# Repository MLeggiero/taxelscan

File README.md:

# TaxelScan v4

Reader board for a 32 × 32 carbon-nanotube tactile mat. Up to eight boards
share one RS-485 harness, start every frame on the same edge, and reach the
host through the first board's USB-C port.

> **Status, 8 Oct 2026:** designed and verified in KiCad. DRC and
> schematic parity are clean, every IC has been checked against its
> datasheet, and the analog chain and USB hot plug have been simulated.
> Fabrication and assembly files are ready; the board is not yet built and
> its firmware not yet written. Every number below is a design value or a
> datasheet value, not a measurement.

| Top | Bottom |
|:---:|:---:|
|  |  |

Plan-view renders of `boards/rev4/rev4.kicad_pcb`, 60.3 × 35.9 mm.

## Key numbers

| | |
|---|---|
| Taxels | 32 × 32 = 1,024 per board; 8,192 on an 8-board harness |
| Converter | the RP2354A's 12-bit SAR ADC, both banks in round robin, 500 ksps |
| Noise *(predicted)* | 1.6–2.3 LSB rms per conversion (ENOB 9.0–9.5) ≈ 8.1–8.6 noise-free bits; the front end adds 0.13 LSB rms |
| Frame rate *(predicted)* | 60 Hz target for 8 boards; 10.9 ms scan, 92 fps ceiling |
| Controller | RP2354A: 2 × Cortex-M33 at 150 MHz, 520 kB SRAM, 2 MB flash in package |
| Board | 60.3 × 35.9 × 1.6 mm, 4 layers, all parts on top |
| Parts | 102 placed (104 on the two end boards), 69 BOM lines, about $15 per board |

## Signal chain

| Stage | Value | Part |
|---|---|---|
| Row drive | 32 rows on the 3.3 V rail; unselected rows held at 0 V | 4 × SN74LVC595A |
| Column select | 2 banks × 16 columns | 2 × CD74HC4067 |
| Sensor, design basis | 1 MΩ at rest, 50 kΩ pressed (assumed) | CNT film |
| Pulldown | 10 kΩ, 0.1 %, 25 ppm/°C | R1, R2 |
| Sense node | 25 mV at rest, 435 mV pressed | |
| Gain | × 6 (10 kΩ / 2 kΩ) | TLV9062 |
| ADC input | 149 mV at rest, 2.61 V pressed; 51 Ω + 1 nF C0G (51 ns) | R21/R22, C31/C32 |
| Reference | ADC_AVDD: the 3.3 V rail through 10 Ω + 100 nF. The rows run from the same rail, so the reading is ratiometric | R26, C36 |
| Converter | 12 bits, ENOB 9.0 min / 9.5 typ; bank A on ADC1 (GPIO27), bank B on ADC3 (GPIO29); the rail monitor on ADC2 | RP2354A |
| 1 LSB | 806 µV at the ADC, 134 µV at the sense node | |
| Counts | about 185 at rest and 3,228 pressed; clipping below 38 kΩ | |
| Settling *(predicted)* | 5.0–6.6 µs to 0.5 LSB with 20 pF of column capacitance | |

## Timing *(predicted)*

| Step | Time |
|---|---|
| One conversion | 2 µs |
| One mux channel, both banks: 6.6 µs settle, a discard and a read per bank, firmware overhead | 19.4 µs |
| One row, 16 channels | 0.32 ms |
| One frame: 32 rows + 2 dark sweeps | 10.9 ms with 20 pF columns (92 fps); 12.0 ms with 50 pF (83 fps) |
| Conditioning 1,024 taxels, second core | ≈ 3.5 ms |
| Sensor to host at 60 Hz | ≈ 22 ms + USB |

## Chain

| | |
|---|---|
| Boards per harness | 8, addressed by 3 solder jumpers (all closed = address 0) |
| Harness | JST GH 6-way (GHR-06V-S housings, SSHL-002T-P0.2 contacts), 26 AWG, 1 A, 4 m planned |
| Wiring | pin n to pin n, from J3 of one board to J4 of the next; J3 and J4 are turned 180° to each other, so the wires cross between boards. Pin 1 is marked at both |
| Pinout | 1 +5 V · 2 GND · 3/4 DATA+/− · 5/6 SYNC+/−, the two pairs twisted |
| Transceivers | 2 × SN65HVD75: 20 Mbps, ±12 kV IEC 61000-4-2 on the bus pins |
| Data pair | half duplex, master polls; 12.5 Mbaud planned (PIO UART), 3 Mbaud for bring-up |
| Sync pair | master sends a 100 µs pulse per frame; every board starts on its falling edge |
| Termination | 120 Ω on the two end boards only |
| Frame size | 1,676 B with a 12-bit map · 140 B contacts only |
| 8 boards at 60 Hz | 804 kB/s with 12-bit maps; the bus 63 % busy |

## Power

| | |
|---|---|
| Input | 5 V from USB-C or the harness, diode-OR (PMEG2005AEA) |
| 3.3 V rail | TPS62162 buck, fixed 3.3 V (3.18–3.43 V); 3–17 V in, 20 V absolute maximum |
| Core rail | RP2354A internal buck with a 3.3 µH AOTA-B201610S3R3, laid out as Raspberry Pi's RP2350A minimal design |
| Draw *(estimate)* | 16–28 mA per board at 5 V, plus about 25 mA while a board transmits |
| Harness feed from USB | 321 mA (285–363) on a 500 mA port; 632 mA (576–697) on a 1.5 A or 3 A Type-C source |
| Boards per feed | 8 on a 500 mA port: seven downstream boards and one transmitter draw 140–225 mA |
| Far end | the eighth board's buck sees about 3.7–4.0 V from a 4.75 V source; it needs 3.3 V |
| Protection | USBLC6-2P6 on D+/D−/VBUS · 0.68 Ω + 22 µF hot-plug damper · PMEG2010ER reverse block |

## Build

| | |
|---|---|
| PCB | JLCPCB, 4 layers, JLC04161H-7628, 1.6 mm, 1 oz outer |
| Rules | 0.10 / 0.10 mm trace/space in the fine-pitch areas, 0.15 / 0.15 elsewhere (four slow nets keep 45 mm at 0.10 mm); copper 0.40 mm from the edge; 300 vias, 0.30 mm drill / 0.50 or 0.60 mm pad |
| Vias | tented: no via hole in an SMD pad but the 9 in U9's and U12's exposed pads and one at U5, so epoxy filling and capping is optional ([design review](boards/rev4/REVIEW.md)) |
| Assembly | Standard PCBA, top side, 0201 smallest; resistors thin film 0.1 %, 25 ppm/°C |
| Files | `boards/rev4/fab/`: `rev4-gerbers.zip`; `rev4-bom.csv` + `rev4-cpl.csv` (102 parts); `-end` pair (104 parts, adds 2 × 120 Ω) |
| Parts cost | about $15 per board for 10 boards at JLCPCB part prices (an estimate, not a quote); PCB and assembly fees extra |
| Programming | USB-C with a BOOTSEL button, or SWD on a 2.54 mm 1 × 4 header in Raspberry Pi's debug order (SC, GND, SD, RUN) |

Order options and what to check in the placement preview:
[`boards/rev4/fab/ORDER-NOTES.txt`](boards/rev4/fab/ORDER-NOTES.txt).

## Verify

```bash
cd boards/rev4
python gen_rev4.py      # writes rev4.net and BOM.csv, asserts every net
python check_faults.py  # injects 41 faults, each must be caught
python make_fab.py      # gerbers, drills, BOM, CPL, drawings
```

| Check | Result |
|---|---|
| Netlist assertions | 134 / 134 nets |
| Fault injection | 42 / 42 behave (41 faults + clean baseline) |
| ERC | 0 errors |
| DRC, zones refilled, schematic parity | 0 unconnected, 0 copper errors |
| Functional review | every IC against its datasheet, the analog chain and hot plug in ngspice: [`boards/rev4/VERIFICATION.md`](boards/rev4/VERIFICATION.md) |

## Open items

| Item | Value to confirm |
|---|---|
| Sensor pressed resistance | 50 kΩ assumed; sets R1/R2 and the gain |
| Column capacitance (mat + FFC) | unmeasured; a 6 µs settle covers about 20 pF |
| ADC noise and bank-to-bank carry-over | raw σ at rest, and whether a conversion must be discarded after each bank switch |
| Hot plug | +5V_USB and the buck input from the stiffest supply; simulated ≤ 6.78 V and ≤ 6.50 V |
| Core rail | VCORE at DVDD pin 23 under load steps, 1.05–1.16 V |
| USB throughput, 8 × 12-bit maps | 804 kB/s against a ≈ 1 MB/s CDC ceiling |
| Firmware | not written; specification in [`firmware/rev3/PLAN.md`](firmware/rev3/PLAN.md), which needs this board's ADC pin map (GPIO27 / 29) |

The smaller items, and what to measure at bring-up, are in
[`boards/rev4/VERIFICATION.md`](boards/rev4/VERIFICATION.md).

Do not flash `firmware/taxelscan/` to this board. It is an earlier board's
sketch and drives GPIO22/23, which are an address strap and the power-fault
input here.

## Repository

```text
boards/rev4/          the board: KiCad project, netlist generator, fab/ package, verification
firmware/rev3/        firmware specification
firmware/rev3_power/  USB power policy, written and unit-tested
libraries/            shared symbols, footprints and 3D models
boards/rev3/, boards/rev1/, firmware/taxelscan/, boards/v2-*/   earlier boards and their firmware
```

`tmp/` and `boards/rev3/backups/` are local working folders and are not in the
repository.

## Credits and license

Sensor pads, electrode geometry and the original readout topology come from the
FlexiTac project. MIT licensed; see [LICENSE](LICENSE).

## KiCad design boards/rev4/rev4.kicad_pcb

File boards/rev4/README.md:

# rev-4 — rev-3 without the external ADC

rev-4 is the rev-3 board (one mat per board, eight boards per harness) with
the LTC1865L 16-bit converter taken out. Both sense banks are read by the
RP2354A's own 12-bit ADC. Everything else — the row drive, the muxes, the ×6
gain stage, the RS-485 harness, the USB-C power path — is rev-3's, at rev-3's
positions, on rev-3's 60.3 × 35.9 mm outline.

| file | what it is |
|---|---|
| `gen_rev4.py`, `check_faults.py` | the netlist generator with its assertions, and the fault-injection proof that they bite (41 faults, all caught). `./gen_rev4.py` writes `rev4.net` and `BOM.csv` |
| `rev4.kicad_pro`, `rev4.kicad_sch`, `rev4.kicad_pcb`, `rev4.kicad_dru`, `fp-lib-table`, `sym-lib-table`, `TaxelScanPower.kicad_sym` | the KiCad 10 project |
| `rev4.net`, `BOM.csv` | generated: the netlist and the bill of materials with LCSC numbers and notes |
| `gen_schematic.py`, `layout_schematic.py`, `make_fab.py`, `kicad_tools.py` | the schematic generator and its drawing, the JLCPCB exporter, pcbnew helpers — rev-3's, retargeted |
| `fab/` | the JLCPCB package from `make_fab.py`: gerbers, drills, `rev4-gerbers.zip`, middle-board and end-board BOM/CPL sets, drawings, order and stackup notes |
| `jlc_placement.csv` | the rotation and origin offset JLCPCB needs for each part, fitted by `tools/jlc_placement.py` from the LCSC parts' own footprints; `make_fab.py` applies it to the CPLs |
| `PLACEMENT.md` | the placement analysis: what removing U8 freed, every move considered, which were made and why |
| `ROUTING_STATUS.md` | the routed board: how it was re-routed for straight routing, DRC, parity, plane health, open items |
| `REVIEW.md` | the 21 October design review: an experienced electrical engineer's six comments on the layout, each measured on the board, and what changed for the ones that hold |
| `VERIFICATION.md` | the functional check: every IC against its datasheet, the analog chain and hot plug simulated, the layout measured, what to fix before ordering and what to measure at bring-up (scripts in `verify/`) |
| `tools/` | the board-change, placement and routing scripts for this revision, and rev-3's router ported to run anywhere (see `tools/README.md`) |
| `pcb_top.png`, `pcb_rev3_vs_rev4.png`, `pcb_routing_before_after.png`, `pcb_review_vias.png` | renders: the board, the ADC corner against rev-3, the routing before and after the re-route, the plane vias before and after the design review |
| `../../libraries/TaxelScan.3dshapes/` | U9's 3D model. KiCad ships none for the QFN-60, so `make_qfn60.py` draws it from the package drawing in the RP2350 datasheet (Fig. 147): 60 leads, one on each pad. J5 shows KiCad's GCT USB4105 body, whose pads match the HRO part's to 0.05 mm |

The design record for everything this revision did not touch — the front-end
reasoning, the USB power design, the audits, the routing history — is in
`../rev3/`, and is not repeated here.

## What changed from rev-3

**Five parts removed.**

| Ref | Part | Job in rev-3 |
|---|---|---|
| U8 | LTC1865LIMS, dual 16-bit SAR, MSOP-10 | the converter, on SPI0 |
| C8 | 1 µF 0402 | U8's VCC bypass |
| R10 | 10 Ω 0402 | U8's reference filter, tapped off ROW_VCC |
| C10 | 10 µF 0805 | the reference reservoir |
| C26 | 10 nF C0G 0402 | the reference's high-frequency bypass |

Parts placed: **109 → 104** on a middle board, **111 → 106** on the two end
boards. Distinct part numbers: **49 → 47** — only the LTC1865LIMS (C580457)
and the 10 nF C0G (C22400107) disappear from the order; C8, R10 and C10 shared
reels with C41, R26 and C9/C39/C46. The low-stock line in rev-3's order notes
(the LTC1865LIMS, 23 in stock) is gone.

**Parts cost.** rev-3's $33.08 per board (10 boards at JLCPCB prices, 28
September 2026) included $18.47 for the LTC1865L. Without it rev-4's parts come
to about **$14.60** a board; the other four parts that went are cents. That is
rev-3's figure less U8's line, not a fresh quote.

**Five nets removed:** `VREF`, `ADC_CONV`, `ADC_SCK`, `ADC_SDI`, `ADC_SDO` —
140 → 135 nets.

**The pin map.** The internal ADC's inputs are GPIO26–29. GPIO26 still cannot
escape (C35, as in rev-3), so:

| signal | rev-3 | rev-4 |
|---|---|---|
| `ADC_A` (bank A) | U8 CH0 | **GPIO27 / ADC1, pin 41** |
| `ADC_B` (bank B) | U8 CH1 | **GPIO29 / ADC3, pin 43** |
| `RAIL_MON` | GPIO28 / ADC2 | GPIO28 / ADC2 (unchanged) |
| `USB_CC_OUT1` | GPIO27 | **GPIO18** (rev-3's `ADC_SCK`) |
| `USB_CC_OUT2` | GPIO29 | **GPIO19** (rev-3's `ADC_SDI`) |
| GPIO16, GPIO17 | `ADC_SDO`, `ADC_CONV` | unused |

`firmware/rev3_power/usb_power_policy.h` takes `-DTAXELSCAN_BOARD_REV=4` for the
rev-4 USB-C pins, and its native test checks both maps at compile time.

**Placement.** Seven parts moved, all in one corner east of the MCU: the two
ADC-input cells (R21/C31, R22/C32) from beside U8 to beside the RP2354A's ADC
pins, and the rail monitor (R15/R16/C45) out of their way. U7 and the gain
network, the muxes, the MCU, the connectors and the outline did not move;
`PLACEMENT.md` has the analysis, including the two moves that were considered
and rejected (moving U7 west, and re-compacting the outline for 0.9 mm). After
the verification, the regulator and buck corners were re-placed and R30 / R31
moved (below).

**Silkscreen.** The back reads `TaxelScan v4`, so the two revisions can be
told apart on the bench. The front has gained a `1` at pin 1 of J3 / J4 and
J6's `SC GND SD RUN` (below).

**Routing.** Re-routed from scratch so that every track runs at 0, 45 or 90
degrees: rev-3's routing, which the first rev-4 kept, had 67 % of its copper at
arbitrary angles; now 0.03 % (0.8 mm of plane ties). Freerouting did the bulk.
The 30 nets it cannot be trusted with were laid first by the board's own
exact-geometry router, octilinear, which also finished and tidied what
Freerouting left:
- the RS-485 pairs and both USB pairs (the USB-C side bridged across J5's
  interleaved pins and run side by side);
- the core regulator as Raspberry Pi lay it out, the buck's input loop, VCORE,
  VREG_LX and SW_NODE;
- the ADC corner, the crystal, J5's VBUS pins and USB_ILIM;
- the corner south and east of the RP2354A, with its address lines, debug
  lines and TUSB320 nets.

Nothing routes on In2 any more (it had 125 mm), so the +3.3 V plane is one
piece. The 5 V rails are 0.3 mm, widened to 0.5-0.6 mm where they fit (bar
D5.5's VBUS tie at 0.15 mm), and VCORE is 0.2 mm.
`ROUTING_STATUS.md` has the method and every number; `pcb_routing_before_after.png`
shows it.

**Rules.** The `U8_escape` rule area and its two custom rules are gone. Six
spots near R22 and D4 had been legal only at that area's 0.10 mm; R22 moved,
and the `USB_ILIM` / `USB_ILIM_LOW` segments were re-routed at the board's
0.15 mm.

## Fixed after the verification (7 October 2026)

`VERIFICATION.md` found three things to deal with before ordering, none of them
new in rev-4, and two smaller ones that were cheap to fix with them. All are
done; the board was re-placed in those two corners (`tools/fix_rev4.py`) and
re-routed from scratch.

**The core regulator, laid out the way Raspberry Pi lay it out** (finding 1).
The RP2350 datasheet (§6.3.8) asks for its Figure 26 "as closely as possible";
rev-3's CIN and COUT sat 5.7–5.9 mm from the pins. Now the parts are at the
offsets from pins 46–50 that Raspberry Pi's RP2350A minimal design uses:

- C44 (CIN) straddles VREG_VIN (pin 49) and VREG_PGND (pin 47); C19 (COUT) is
  beside it; L1 is above, its polarity dot on VCORE. Both capacitors are now
  0402 4.7 µF (Samsung CL05A475MP5NRNC; the minimal design fits Murata's 6.3 V
  GRM155R60J475ME47D) on the minimal design's wide-gap land
  (`FlexiTac:C_0402_1005Metric_WideGap`), so VREG_LX runs straight up from pin
  48 between their pads into L1: 3.3 mm on F.Cu with no via (it was 4.4 mm).
- CIN's and COUT's grounds join pin 47 and reach the plane at one point,
  through two adjacent vias. CFILT (C43, now 0402 too) has its own ground via.
  VREG_FB is taken from COUT's pad, beside LX rather than under it. VCORE
  leaves through two vias west of COUT. In1 is cut away under L1 and the LX
  track (Figure 27).
- The switching loop, LX → L1 → COUT → ground → PGND, encloses 2.6 mm²
  (`verify/layout/vreg_loop.py`), against about 20 mm² before and 2.3 mm² in
  the minimal design measured the same way.
- R23 / R24, the USB series resistors, moved north-west of pins 51 / 52 as in
  the minimal design, so USB_D leaves on F.Cu with no via: 4.1 / 3.8 mm,
  where it was 5.7 / 4.8 mm through two vias each.
- Pins 53 and 54 (USB_OTP_VDD, QSPI_IOVDD) are tied in the ring and share C18,
  1.3 mm of track from pin 54 with its own ground via. That also settles
  finding 4. C17, no longer needed at VREG_VIN,
  decouples the VREG_AVDD filter's +3.3 V input.

**Hot plug** (finding 2). The new simulation (`verify/power/damper.py`) took
the supply to USB-C's 5.5 V maximum. There, with a 1.5 µH captive cable, the
old damper left U12's input at 7.06 V against the TLV62569's 6 V absolute
maximum, and +5V_USB at 7.36 V against U14's 7 V. No damper inside USB's
attach-capacitance limits keeps a 6 V part safe, so:

- U12 is now TI's TPS62162 (LCSC C40256): the fixed 3.3 V member of the
  TPS6216x, 3–17 V in, 20 V absolute maximum. It runs at 100 % duty cycle at
  the far end of the harness and has the same 2.2 µH / 22 µF output as before
  (TI's standard pairing). The fixed output takes R18 / R19 off the board.
  It is laid out as TI's Figure 42: C27 across VIN / PGND at the pins, C22
  beside them, AGND, PGND and C22's ground meeting at the exposed pad (two
  vias), L2 beside SW (2.5 mm of 0.3 mm track, was 4.3 mm), VOS from L2's
  output pad.
- The damper is now R38 0.68 Ω + C46 22 µF (the C23 reel). +5V_USB stays at
  or below 6.78 V in every case simulated: 5.0–5.5 V supplies, 0.5–2 µH
  cables. That is inside U14's 7 V. U12's input now peaks at 6.5 V against
  20 V. The cost is about 5 µF more effective attach capacitance, behind 0.68 Ω.

**The harness cable** (finding 3). J3 and J4 are the same part turned 180° to
each other, so a cable laid straight across between two boards joins pin 1 to
pin 6. That puts +5V_BUS on SYNC_N, and the next board gets no power. The
cable is:

| J3 / J4 pin | net | cable |
|---|---|---|
| 1 | +5V_BUS | marked `1` on the silkscreen at both connectors |
| 2 | GND | |
| 3 / 4 | BUS_P / BUS_N | twisted pair |
| 5 / 6 | SYNC_P / SYNC_N | twisted pair |

It uses JST GH parts: a GHR-06V-S housing at each end, SSHL-002T-P0.2
contacts and 26 AWG wire. It is wired **pin n to pin n**, from J3 of one board
to J4 of the next, so the wires cross between adjacent boards. Ring J3.1 to
J4.1 before connecting power. The end boards carry R11 / R12 (the `-end` CPL).

**The debug header** (finding 10). J6 is now SWCLK, GND, SWDIO, RUN (pins
1–4): Raspberry Pi's 3-pin debug connector order (SC, GND, SD) on pins 1–3,
so the Debug Probe's lead fits pin 1 to pin 1. The silkscreen reads
`SC GND SD RUN` above the pins.

**Firmware** (finding 11). `firmware/rev3_power/usb_power_policy.h` no longer
defaults to rev-3. It stops the build with `#error` unless
`TAXELSCAN_BOARD_REV` is 3 or 4.

**For the re-route**, R30 / R31 (U14's EN pull-down and FAULT pull-up) moved
from west of U9 to under U14's pins 3 and 4. Where rev-3 left them, both nets
crossed under the MCU to reach them (38–52 mm, 4–6 vias), and the rip-up loop
could not fit them past U9's east side. Now they are 20 and 26 mm, with 2 vias
and none.

Placed parts: 104 → 102 on a middle board, 106 → 104 on the two end boards. Nets: 135 → 134 (`FB` went with the divider).
Distinct part numbers: 47 → 46.

## What the internal ADC changes, electrically

- **The reference.** The RP2350-family ADC has no reference of its own and
  converts against its supply pin, `ADC_AVDD`. Here that is +3.3 V through R26
  (10 Ω) with C36 (100 nF) at the pin; ROW_VCC, the row excitation, is +3.3 V
  through R5 (0 Ω). Reference and excitation are two branches of one rail, so
  the reading stays ratiometric, as rev-3's ROW_VCC-tapped VREF made it. The ADC
  draws about 150 µA from `ADC_AVDD` (Raspberry Pi's Pico 2 datasheet quotes the
  30 mV this costs across that board's 201 Ω filter), so R26's drop is ~1.5 mV:
  a fixed 0.05 % gain error, small beside the 0.1 % resistors that set the
  gain. rev-3's R10/C10 held its reference quiet above ~1.6 kHz; R26/C36 corner
  at ~160 kHz, so the reference now tracks the excitation over a wider band -
  rail noise common to both cancels instead of appearing in the reading - while
  R26 still keeps IOVDD switching noise off it.
- **Resolution.** `../rev3/ROUTING_STATUS.md` estimated the 16-bit chain at
  ~11.9 noise-free bits at 80 fps. The internal ADC's ENOB is 9.0 minimum,
  9.5 typical (RP2350 datasheet Table 1685): 1.6-2.3 LSB rms, 8.1-8.6 noise-free
  bits per conversion. That is 10-14× more noise per conversion than rev-3
  expected, before oversampling and the conditioning filters - the same converter
  rev-1, the board that has shipped, reads its mat with. The front end adds only
  0.13 LSB rms (`VERIFICATION.md`). The ×6 gain stage, which is where rev-3's
  sensitivity gain over rev-1 comes from, stays.
- **One converter for both banks.** The internal ADC is a single SAR behind an
  input mux, as on rev-1, where reading bank A then bank B let charge carry over
  and the firmware's `adcDiscard` throws one conversion away after a switch.
  rev-1 had nothing at the pins; here each pin has its 1 nF reservoir, far
  larger than the sampling capacitor, so the carried charge is shared into the
  reservoir instead of landing on a bare high-impedance node. Keep `adcDiscard`
  until bring-up measures it (rev-1's test 0c).
- **Firmware.** No LTC1865L driver to write: `firmware/rev3/PLAN.md` §3.3 and the
  SPI0 transfer sequence fall away. Its count domain (D2) already scales the
  16-bit code down to rev-1's 12-bit count, 806 µV at the ADC, so the internal
  ADC gives the same count with `adcShift = 0`, and the conditioning pipeline and
  the simulator's golden digest are unaffected. rev-1's `scan.cpp` internal-ADC
  path carries over with the new channels (ADC1 / ADC3).

## How it was built, and what was checked

    ./gen_rev4.py                  rev4.net + BOM.csv: 134 of 134 nets check out
    ./check_faults.py              41 injected faults all caught, clean baseline passes (42 of 42)
    ./gen_schematic.py             rev4.kicad_sch: 134 of 134 nets match, before and after the
                                   KiCad 10 upgrade; 107 parts agree with BOM.csv; ERC 0 errors
    tools/eco_rev4.py              rev3.kicad_pcb -> rev4.kicad_pcb: rip, delete, re-pin
    tools/place_rev4.py            the seven moves, each placed and routed
    tools/route_rev4.py            AMP_A/B, +5V, USB_CC_OUT1/2, the ILIM fixes, FID2; prune
    tools/fix_rev4.py              the verification fixes: regulator corner, TPS62162, J6, silk; R30 / R31
    tools/freeroute_rev4.py all    the re-route: strip, pre-route, freerouting, import, finish
    tools/review_rev4.py           the design review's changes (REVIEW.md): edge, vias, widths, corners
    tools/finalize_rev4.py         install, then KiCad DRC with zones refilled + schematic parity
    ./make_fab.py                  fab/

| Check (KiCad 10.0.7) | Result |
|---|---|
| DRC, zones refilled | 0 unconnected, 0 copper errors under the design review's rules (copper 0.40 mm from the edge, via holes 0.10 mm clear of SMD pads, 0.15 mm track outside the escape areas); rev-3's same 5 silkscreen warnings |
| Schematic parity | every net's pads match; the only items are rev-3's net-name prefix and J5's two open SBU pins |
| ERC | 0 errors |
| Routing | 0.8 of 2306 mm (0.03 %) off 0 / 45 / 90 degrees, all of it plane ties (first rev-4: 67 %); nothing on In2; 169 signal vias; no via hole in an SMD pad but the exposed pads' 9 (U5 pin 15's pad toe cut back 0.30 mm, 26 October); 8 bare right angles, none on the pairs; the USB-C data pair 2 / 2 vias, side by side |
| +3.3 V plane (In2) | 1 piece, 1840 mm², all 31 vias (the 8 October board, filled the same way with KiCad 10.0.7: 1841 mm²; first rev-4: 2 pieces, 1740 mm², 33 of 34; rev-3: 7 pieces, 1665 mm², 27 of 35) |
| GND plane (In1) | one piece, 1875 mm², all 100 vias (8 October, filled the same way: 1879 mm², 104 vias) |
| Fab package | 69 BOM lines, every one with an LCSC number; 102 / 104 parts in the CPLs; both planes in the gerbers |
| Firmware pin map | `firmware/rev3_power` native test passes for rev-3 and rev-4; a build without `TAXELSCAN_BOARD_REV` stops |

What is still open, and what to measure at bring-up: `VERIFICATION.md` and `ROUTING_STATUS.md`.

The board scripts run with KiCad's Python (`pcbnew`); `tools/README.md` says how.
The intermediate boards live in `<checkout>/tmp/` (git-ignored).

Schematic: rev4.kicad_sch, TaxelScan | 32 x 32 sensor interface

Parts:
C1, C2, C3, C4, C5, C6, C7, C12, C27, C28, C29, C38, C40, C42, C45: 100nF; C_0402_1005Metric
C9, C39: 10uF; C_0805_2012Metric
C11, C13, C14, C15, C16, C17, C18, C24, C25, C33, C34, C35, C36: 100nF; C_0201_0603Metric
C19, C44: 4.7uF; C_0402_1005Metric_WideGap
C20, C21: 15pF; C_0402_1005Metric
C22: 4.7uF; C_0603_1608Metric
C23, C46: 22uF; C_0805_2012Metric
C31, C32: 1nF; C_0402_1005Metric
C37: 1uF; C_0805_2012Metric
C41: 1uF; C_0402_1005Metric
C43: 4.7uF; C_0402_1005Metric
D1, D2: PMEG2005AEA; D_SOD-323
D3: LED_Green; LED_0603_1608Metric
D4: PMEG2010ER; Nexperia_CFP3_SOD-123W
D5: USBLC6-2P6; SOT-666
J1, J2: FFC_32P_0.5mm; FFC_0.5mm_FH12_32_16_12way_Composite
J3, J4: Bus_6P; JST_GH_SM06B-GHS-TB_1x06-1MP_P1.25mm_Horizontal
J5: USB-C; USB_C_Receptacle_HRO_TYPE-C-31-M-12
J6: SWD; PinHeader_1x04_P2.54mm_Vertical
JP1, JP2, JP3: ADDR; SolderJumper-2_P1.3mm_Bridged_Pad1.0x1.5mm
L1: AOTA-B201610S3R3-101-T; L_0806_2016Metric
L2: 2.2uH; L_1210_3225Metric
Q1: 2N7002PW; SOT-323_SC-70
R1, R2, R6, R8, R20, R31, R32, R33, R37: 10k; R_0402_1005Metric
R3, R4, R35: 33R; R_0402_1005Metric
R5: 0R; R_0402_1005Metric
R7, R9: 2k; R_0402_1005Metric
R11, R12: 120R; R_0603_1608Metric
R15: 100k; R_0402_1005Metric
R16: 47k; R_0402_1005Metric
R17, R25, R36: 1k; R_0402_1005Metric
R21, R22: 51R; R_0402_1005Metric
R23, R24: 27R; R_0402_1005Metric
R26: 10R; R_0402_1005Metric
R27, R28: 82.5k; R_0402_1005Metric
R29, R30: 4.7k; R_0402_1005Metric
R34: 866k; R_0402_1005Metric
R38: 0.68R; R_0603_1608Metric
SW1: BOOTSEL; SW_SPST_B3U-1000P
U1, U2, U3, U4: SN74LVC595APW; TSSOP-16_4.4x5mm_P0.65mm
U5, U6: CD74HC4067SM96; SSOP-24_5.3x8.2mm_P0.65mm
U7: TLV9062IDGKR; MSOP-8_3x3mm_P0.65mm
U9: RP2354A; QFN-60-1EP_7x7mm_P0.4mm_EP3.4x3.4mm
U10, U11: SN65HVD75DR; SOIC-8_3.9x4.9mm_P1.27mm
U12: TPS62162DSGR; Texas_DSG0008A_WSON-8-1EP_2x2mm_P0.5mm_EP0.9x1.6mm
U13: TUSB320LAIRWBR; Texas_X2QFN-12_1.6x1.6mm_P0.4mm
U14: TPS2553DBVR; SOT-23-6
Y1: ABM8-272-T3; Crystal_SMD_3225-4Pin_3.2x2.5mm

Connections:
+3.3V: C5.1, C6.1, C7.1, C9.1, C11.1, C12.1, C13.1, C14.1, C15.1, C17.1, C18.1, C23.1, C28.1, C29.1, C33.1, C34.1, C40.1, C41.1, C44.1, L2.2, R5.1, R20.2, R26.1, R31.2, R32.2, R33.2, R35.1, U5.24 (VCC), U6.24 (VCC), U7.8 (V+), U9.1 (IOVDD), U9.11 (IOVDD), U9.20 (IOVDD), U9.30 (IOVDD), U9.38 (IOVDD), U9.45 (IOVDD), U9.49 (VREG_VIN), U9.53 (USB_OTP_VDD), U9.54 (QSPI_IOVDD), U10.8 (VCC), U11.8 (VCC), U12.6 (VOS), U13.12 (VDD)
+5V: C22.1, C27.1, D1.1 (K), D2.1 (K), R15.1, U12.2 (VIN), U12.3 (EN)
+5V_BUS: C39.1, D1.2 (A), D4.1 (K), J3.1, J4.1
+5V_USB: C37.1, C38.1, C42.1, D2.2 (A), D5.5 (VBUS), J5.A4 (VBUS), J5.A9 (VBUS), J5.B4 (VBUS), J5.B9 (VBUS), R34.1, R38.1, U14.1 (IN)
ADC_A: C31.1, R21.2, U9.41 (GPIO27/ADC1)
ADC_AVDD: C36.1, R26.2, U9.44 (ADC_AVDD)
ADC_B: C32.1, R22.2, U9.43 (GPIO29/ADC3)
ADDR0: JP1.1 (A), U9.32 (GPIO20)
ADDR1: JP2.1 (A), U9.33 (GPIO21)
ADDR2: JP3.1 (A), U9.34 (GPIO22)
AMP_A: R6.2, R21.1, U7.1
AMP_B: R8.2, R22.1, U7.7
BOOTSEL: R25.1, U9.60 (~QSPI_SS)
BOOTSEL_SW: R25.2, SW1.1
BUS_DE: U9.14 (GPIO10), U10.2 (~RE), U10.3 (DE)
BUS_DI: U9.12 (GPIO8), U10.4 (DI)
BUS_N: J3.4, J4.4, R11.2, U10.7 (B)
BUS_P: J3.3, J4.3, R11.1, U10.6 (A)
BUS_RO: U9.13 (GPIO9), U10.1 (RO)
COL_0: J2.1, U5.9 (I0)
COL_1: J2.2, U5.8 (I1)
COL_2: J2.3, U5.7 (I2)
COL_3: J2.4, U5.6 (I3)
COL_4: J2.5, U5.5 (I4)
COL_5: J2.6, U5.4 (I5)
COL_6: J2.7, U5.3 (I6)
COL_7: J2.8, U5.2 (I7)
COL_8: J2.9, U5.23 (I8)
COL_9: J2.10, U5.22 (I9)
COL_10: J2.11, U5.21 (I10)
COL_11: J2.12, U5.20 (I11)
COL_12: J2.13, U5.19 (I12)
COL_13: J2.14, U5.18 (I13)
COL_14: J2.15, U5.17 (I14)
COL_15: J2.16, U5.16 (I15)
COL_16: J2.17, U6.9 (I0)
COL_17: J2.18, U6.8 (I1)
COL_18: J2.19, U6.7 (I2)
COL_19: J2.20, U6.6 (I3)
COL_20: J2.21, U6.5 (I4)
COL_21: J2.22, U6.4 (I5)
COL_22: J2.23, U6.3 (I6)
COL_23: J2.24, U6.2 (I7)
COL_24: J2.25, U6.23 (I8)
COL_25: J2.26, U6.22 (I9)
COL_26: J2.27, U6.21 (I10)
COL_27: J2.28, U6.20 (I11)
COL_28: J2.29, U6.19 (I12)
COL_29: J2.30, U6.18 (I13)
COL_30: J2.31, U6.17 (I14)
COL_31: J2.32, U6.16 (I15)
GAIN_A: R6.1, R7.1, U7.2 (-)
GAIN_B: R8.1, R9.1, U7.6 (-)
GND: C1.2, C2.2, C3.2, C4.2, C5.2, C6.2, C7.2, C9.2, C11.2, C12.2, C13.2, C14.2, C15.2, C16.2, C17.2, C18.2, C19.2, C20.2, C21.2, C22.2, C23.2, C24.2, C25.2, C27.2, C28.2, C29.2, C31.2, C32.2, C33.2, C34.2, C35.2, C36.2, C37.2, C38.2, C39.2, C40.2, C41.2, C42.2, C43.2, C44.2, C45.2, C46.2, D3.1 (K), D5.2 (GND), J1.MP (MountPin), J2.MP (MountPin), J3.2, J3.MP (MountPin), J4.2, J4.MP (MountPin), J5.A1 (GND), J5.A12 (GND), J5.B1 (GND), J5.B12 (GND), J5.SH (SHIELD), J6.2, JP1.2 (B), JP2.2 (B), JP3.2 (B), Q1.2 (S), R1.2, R2.2, R7.2, R9.2, R16.2, R27.2, R29.2, R30.2, R37.2, SW1.2, U1.8 (GND), U1.13 (~OE), U2.8 (GND), U2.13 (~OE), U3.8 (GND), U3.13 (~OE), U4.8 (GND), U4.13 (~OE), U5.12 (GND), U5.15 (~E), U6.12 (GND), U6.15 (~E), U7.4 (V-), U9.47 (VREG_PGND), U9.61 (GND), U10.5 (GND), U11.2 (~RE), U11.4 (DI), U11.5 (GND), U12.1 (PGND), U12.4 (AGND), U12.5 (FB), U12.9 (PAD), U13.3 (PORT), U13.10 (GND), U13.11 (~EN), U14.2 (GND), Y1.2 (G), Y1.4 (G)
LED_A: D3.2 (A), R17.2
MUX_S0: U5.10 (S0), U6.10 (S0), U9.7 (GPIO4)
MUX_S1: U5.11 (S1), U6.11 (S1), U9.8 (GPIO5)
MUX_S2: U5.14 (S2), U6.14 (S2), U9.9 (GPIO6)
MUX_S3: U5.13 (S3), U6.13 (S3), U9.10 (GPIO7)
RAIL_MON: C45.1, R15.2, R16.1, U9.42 (GPIO28/ADC2)
ROW_0: J1.1, U1.15 (QA)
ROW_1: J1.2, U1.1 (QB)
ROW_2: J1.3, U1.2 (QC)
ROW_3: J1.4, U1.3 (QD)
ROW_4: J1.5, U1.4 (QE)
ROW_5: J1.6, U1.5 (QF)
ROW_6: J1.7, U1.6 (QG)
ROW_7: J1.8, U1.7 (QH)
ROW_8: J1.9, U2.15 (QA)
ROW_9: J1.10, U2.1 (QB)
ROW_10: J1.11, U2.2 (QC)
ROW_11: J1.12, U2.3 (QD)
ROW_12: J1.13, U2.4 (QE)
ROW_13: J1.14, U2.5 (QF)
ROW_14: J1.15, U2.6 (QG)
ROW_15: J1.16, U2.7 (QH)
ROW_16: J1.17, U3.15 (QA)
ROW_17: J1.18, U3.1 (QB)
ROW_18: J1.19, U3.2 (QC)
ROW_19: J1.20, U3.3 (QD)
ROW_20: J1.21, U3.4 (QE)
ROW_21: J1.22, U3.5 (QF)
ROW_22: J1.23, U3.6 (QG)
ROW_23: J1.24, U3.7 (QH)
ROW_24: J1.25, U4.15 (QA)
ROW_25: J1.26, U4.1 (QB)
ROW_26: J1.27, U4.2 (QC)
ROW_27: J1.28, U4.3 (QD)
ROW_28: J1.29, U4.4 (QE)
ROW_29: J1.30, U4.5 (QF)
ROW_30: J1.31, U4.6 (QG)
ROW_31: J1.32, U4.7 (QH)
ROW_CLK: R3.2, U1.11 (SRCLK), U2.11 (SRCLK), U3.11 (SRCLK), U4.11 (SRCLK)
ROW_CLK_MCU: R3.1, U9.4 (GPIO2)
ROW_DATA: U1.14 (SER), U9.5 (GPIO3)
ROW_LATCH: R4.2, U1.12 (RCLK), U2.12 (RCLK), U3.12 (RCLK), U4.12 (RCLK)
ROW_LATCH_MCU: R4.1, U9.3 (GPIO1)
ROW_VCC: C1.1, C2.1, C3.1, C4.1, R5.2, U1.10 (~SRCLR), U1.16 (VCC), U2.10 (~SRCLR), U2.16 (VCC), U3.10 (~SRCLR), U3.16 (VCC), U4.10 (~SRCLR), U4.16 (VCC)
RUN: J6.4, R20.1, U9.26 (RUN)
SENSE_A: R1.1, U5.1 (COM), U7.3 (+)
SENSE_B: R2.1, U6.1 (COM), U7.5 (+)
SR_CHAIN_1: U1.9 (QH'), U2.14 (SER)
SR_CHAIN_2: U2.9 (QH'), U3.14 (SER)
SR_CHAIN_3: U3.9 (QH'), U4.14 (SER)
STATUS: R17.1, U9.37 (GPIO25)
SWCLK: J6.1, U9.24 (SWCLK)
SWDIO: J6.3, U9.25 (SWDIO)
SW_NODE: L2.1, U12.7 (SW)
SYNC_DE: R37.1, U9.17 (GPIO13), U11.3 (DE)
SYNC_N: J3.6, J4.6, R12.2, U11.7 (B)
SYNC_OUT: U9.15 (GPIO11), U11.1 (RO)
SYNC_P: J3.5, J4.5, R12.1, U11.6 (A)
USBC_D_N: D5.3 (I/O2), D5.4 (I/O2), J5.A7 (D-), J5.B7 (D-), R24.2
USBC_D_P: D5.1 (I/O1), D5.6 (I/O1), J5.A6 (D+), J5.B6 (D+), R23.2
USB_BUS_EN: R30.1, U9.36 (GPIO24), U14.3 (EN)
USB_BUS_SW: D4.2 (A), U14.6 (OUT)
USB_CC1: J5.A5 (CC1), U13.1 (CC1)
USB_CC2: J5.B5 (CC2), U13.2 (CC2)
USB_CC_OUT1: R32.1, U9.29 (GPIO18), U13.7 (SDA/OUT1)
USB_CC_OUT2: R33.1, U9.31 (GPIO19), U13.8 (SCL/OUT2)
USB_D_N: R24.1, U9.51 (USB_DM)
USB_D_P: R23.1, U9.52 (USB_DP)
USB_ILIM: R27.1, R28.1, U14.5 (ILIM)
USB_ILIM_HI: Q1.1 (G), R29.1, U9.2 (GPIO0)
USB_ILIM_LOW: Q1.3 (D), R28.2
USB_PWR_FAULT: R31.1, U9.35 (GPIO23), U14.4 (~FAULT)
USB_SNUB: C46.1, R38.2
USB_VBUS_DET: R34.2, U13.4 (VBUS_DET)
VCORE: C19.1, C24.1, C25.1, C35.1, L1.1, U9.6 (DVDD), U9.23 (DVDD), U9.39 (DVDD), U9.50 (VREG_FB)
VREG_AVDD: C16.1, C43.1, R35.2, U9.46 (VREG_AVDD)
VREG_LX: L1.2, U9.48 (VREG_LX)
XIN: C20.1, U9.21 (XIN), Y1.1
XOUT: C21.1, R36.2, Y1.3
XOUT_MCU: R36.1, U9.22 (XOUT)

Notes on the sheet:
TAXELSCAN / REV 4
32 x 32 matrix > two sense banks > RP2354A internal 12-bit ADC > RS-485 harness
01 ROW EXCITATION
MCU serial stream > four latched drivers > 32-way row FFC
02 COLUMN SENSING
32 columns > two 16:1 muxes > gain of 6 > filtered inputs to the MCU ADC
03 SCAN CONTROLLER
RP2354A / clock / core supply / local bypass
04 POWER + RAIL MONITOR
Harness or USB power > diode OR > local 3.3 V buck
05 COMMUNICATIONS + BOARD ADDRESS
Half-duplex data pair and dedicated receive-only sync pair
06 USB + PROGRAMMING
USB-C data / configuration straps / SWD / BOOTSEL
Rows 0-7
Rows 8-15
Rows 16-23
Rows 24-31
ROW FFC
Pin n = ROW_(n-1) Mounting pad = GND
Serial order: U1 > U2 > U3 > U4 Outputs enabled; unselected rows held LOW.
Clock / latch damping
U1-U4 bypass
Excitation rail link
COLUMN FFC
Pin n = COL_(n-1) Mounting pad = GND
R1/R2: 10k pulldown Rf/Rg: 10k / 2k (G = 6)
51R / 1nF at each MCU ADC pin Series resistors outside feedback
ADC_A > U9 GPIO27 / ADC1 (pin 41) ADC_B > U9 GPIO29 / ADC3 (pin 43)
The converter is the RP2354A (section 03). Its reference is ADC_AVDD, filtered off +3.3V by R26 / C36 (section 04); ROW_VCC is the same rail through R5, so the code stays ratiometric.
ROW_* > section 01 MUX_*, ADC_* > section 02 BUS_*, SYNC_* > section 05 USB_*, SWD* > section 06
Unused GPIO / stacked-flash pins are marked with no-connects.
R36: 1k XOUT series, limits crystal drive
12 MHz / C0G load capacitors
VREG_AVDD: 33R / 4.7uF filter
Core regulator / DVDD bypass
MCU 3.3 V bypass
3.3 V buck: TPS62162, fixed output 3-17 V in, 20 V absolute maximum
5 V rail monitor 100k / 47k divider to MCU
MCU ADC supply and reference filter

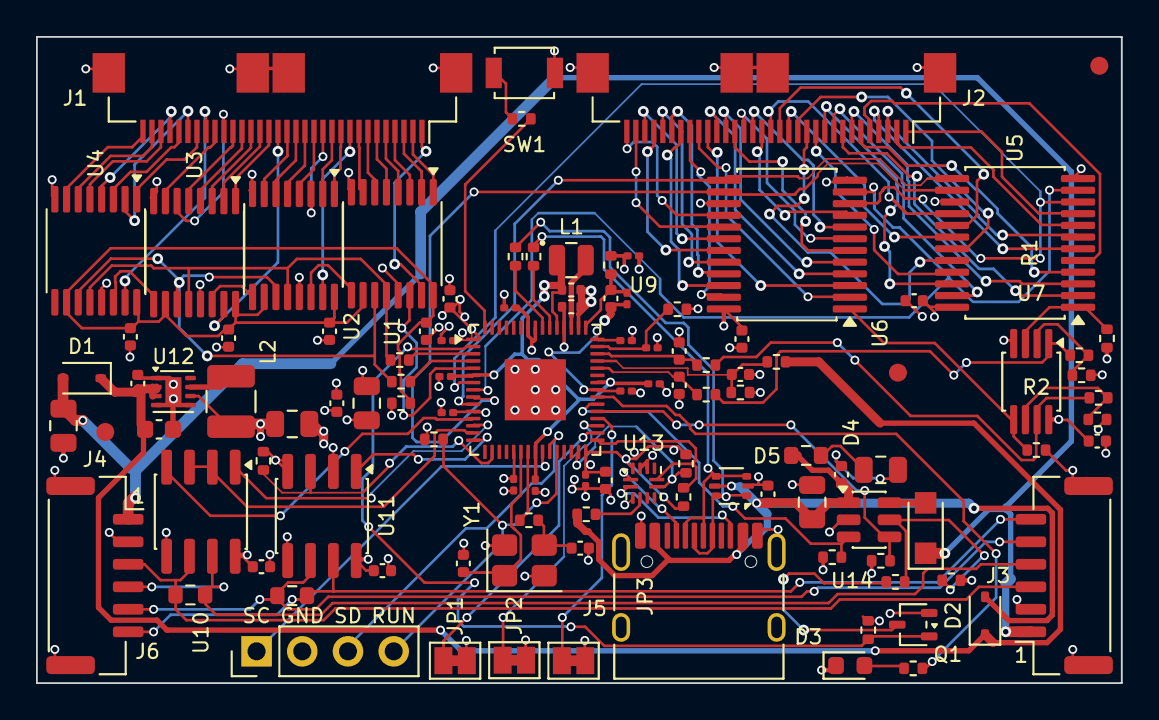
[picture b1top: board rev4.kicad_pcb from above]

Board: 4 copper layers, 60.3 x 35.9 mm, 110 parts (0 on the bottom side), 134 nets.

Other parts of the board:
FID1, FID2, FID3: Fiducial; Fiducial_1mm_Mask2mm

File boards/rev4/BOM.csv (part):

Reference,Value,Footprint,LCSC,Note
U1-U4,SN74LVC595APW,Package_SO:TSSOP-16_4.4x5mm_P0.65mm,C52287685,"32 row drivers; unselected rows held LOW. TI SN74LVC595APWR. (Was C6062, which is a 74LVC138 decoder.)"
"U5,U6",CD74HC4067SM96,Package_SO:SSOP-24_5.3x8.2mm_P0.65mm,C98457,"32 columns, 2 banks of 16"
U7,TLV9062IDGKR,Package_SO:MSOP-8_3x3mm_P0.65mm,C398356,"Gain stage, was a unity-gain follower. TI TLV9062IDGKR: DGK = VSSOP-8 on 0.65 mm, which is what this footprint is (the D suffix is SOIC-8 and does NOT fit)."
U9,RP2354A,Package_DFN_QFN:QFN-60-1EP_7x7mm_P0.4mm_EP3.4x3.4mm,C41378174,"NEW: replaces the XIAO module; 2 MB flash stacked in package. Thermal vias are added at layout at 0.3 mm - the library's _ThermalVias variant uses 0.2 mm, below JLCPCB's standard tier"
U10,SN65HVD75DR,Package_SO:SOIC-8_3.9x4.9mm_P1.27mm,C57928,"NEW: RS-485 data, half duplex"
U11,SN65HVD75DR,Package_SO:SOIC-8_3.9x4.9mm_P1.27mm,C57928,"NEW: RS-485 sync, receive only (DE and DI strapped low)"
U12,TPS62162DSGR,Package_SON:Texas_DSG0008A_WSON-8-1EP_2x2mm_P0.5mm_EP0.9x1.6mm,C40256,"5 V -> 3.3 V buck, FIXED 3.3 V output (the 62161 is 1.8 V and the 62163 5 V, so the suffix is the rail voltage). TI TPS62162DSGR: 3-17 V in, 20 V absolute maximum, so the USB-C hot-plug ring (to 7.4 V on +5V_USB, VERIFICATION.md finding 2) cannot overstress it; 100% duty cycle at the far end of the harness; UVLO 2.6-2.82 V. Thermal vias are added at layout at 0.3 mm. (Was C141836, the TLV62569DBVR, 6 V absolute maximum; before that C144206, a MIC2954 LDO in SOT-223.)"
U13,TUSB320LAIRWBR,Package_DFN_QFN:Texas_X2QFN-12_1.6x1.6mm_P0.4mm,C132554,"USB-C sink/current detection, GPIO mode; LAI required for dynamic current updates. Same 12-pin map as stock TUSB320 symbol; internal Rd replaces R13/R14"
U14,TPS2553DBVR,Package_TO_SOT_SMD:SOT-23-6,C55266,USB-to-harness current-limited switch; default OFF. TI TPS2553DBVR - not the -1 variant. R27=82.5k; Q1 switches R28 in parallel for higher CC budget
Q1,2N7002PW,Package_TO_SOT_SMD:SOT-323_SC-70,C255579,Select high harness current limit only after CC advertises >=1.5A
D4,PMEG2010ER,Diode_SMD:Nexperia_CFP3_SOD-123W,C82288,Nexperia PMEG2010ER. 1A series reverse barrier: U14 OUT anode -> harness cathode. Prevents powered harness backfeeding USB even during U14 reverse-comparator delay
"R27,R28",82.5k,Resistor_SMD:R_0402_1005Metric,C852928,"Current-limit resistors; nominal 321 mA / 632 mA, tolerance bounds in USB_POWER.md. THIN FILM 0.1% 25ppm/C (Yageo RT0402BRD0782K5L)"
"R29,R30",4.7k,Resistor_SMD:R_0402_1005Metric,C281778,Pulldowns: current-select gate / harness enable; reset and unpowered MCU leave harness feed OFF. THIN FILM 0.1% 25ppm/C (Yageo RT0402BRD074K7L)
R31-R33,10k,Resistor_SMD:R_0402_1005Metric,C844452,"3.3V pullups: power fault and CC OUT1/OUT2; same supply as U13 prevents backpower. THIN FILM 0.1% 25ppm/C (Vishay TNPW040210K0BEED, the same reel as every 10k)"
R34,866k,Resistor_SMD:R_0402_1005Metric,C149916,"VBUS_DET series resistor. THIN FILM 0.5% 50ppm/C (Ever Ohms TR0402D866KQ1050): 861.7-870.3k, inside the TUSB320's 855-920k window. No 0402 thin-film 887k is stocked; 887k 1% thick film (Panasonic ERJ-2RKF8873X, C409935) is the fallback"
"C40,C42",100nF,Capacitor_SMD:C_0402_1005Metric,C85858,"Local bypass at U13 VDD / U14 IN. Murata GCM155R71H104KE02D, X7R 50 V, AEC-Q200"
C41,1uF,Capacitor_SMD:C_0402_1005Metric,C52923,"U13 local supply reservoir. Samsung CL05A105KA5NQNC, X5R 25 V"
D5,USBLC6-2P6,Package_TO_SOT_SMD:SOT-666,C15999,"USB ESD: D+, D- and VBUS clamped at the connector, on the connector side of R23/R24. ST USBLC6-2P6 (SOT-666, 3.5 pF per line, 17 V at 5 A). The RP2354A's USB pins carry HBM protection only. The RS-485 bus pins need no external part: the SN65HVD75 has +-12 kV IEC 61000-4-2 contact protection on chip. CC1/CC2 rely on the TUSB320's +-7 kV HBM"
R38,0.68R,Resistor_SMD:R_0603_1608Metric,C27862,"Hot-plug damper, first element in series with C46 across +5V_USB. A live USB cable into ceramic-only input capacitance rings to nearly twice VBUS. Simulated (verify/power/damper.py) from a 5.5 V supply on a 1.5 uH / 0.08 R captive cable, 0.68R + 22uF holds +5V_USB to 6.8 V, inside U14's 7 V absolute maximum; 1R + 10uF let it reach 7.4 V. 0.68R is near sqrt(L/C) of that cable into ~4 uF. Takes ~0.17 mJ per plug-in (6.8 A peak for a few us). THICK FILM 1% 0603 (UNI-ROYAL 0603WAF680LT5E): thick film takes the pulse better than thin, and the value's tolerance does not matter here. (Was 1R, C861215)"
C46,22uF,Capacitor_SMD:C_0805_2012Metric,C45783,"Hot-plug damper reservoir, behind R38 so it damps the ring instead of joining it; about 12 uF at 5 V. Samsung CL21A226MAQNNNE, X5R 25 V, the same reel as C23. (Was 10uF, C3039694)"
"R1,R2",10k,Resistor_SMD:R_0402_1005Metric,C844452,"Sense pulldowns, changed from 3.3k. FIT ON TEST. THIN FILM 0.1% 25ppm/C (Vishay TNPW040210K0BEED) - these set the transfer function, and an R1/R2 tempco mismatch is a bank-to-bank GAIN drift, which the dark reference cannot remove"
"R3,R4",33R,Resistor_SMD:R_0402_1005Metric,C852729,SRCLK/RCLK damping. THIN FILM 0.1% 25ppm/C (Yageo RT0402BRD0733RL)
R5,0R,Resistor_SMD:R_0402_1005Metric,C2654001,"+3.3V -> ROW_VCC link, the excitation rail's own branch of +3.3V; the ADC reference (ADC_AVDD) is the other branch, through R26. Vishay MCS04020Z0000ZE000, a thin-film 0R jumper"
"R6,R8",10k,Resistor_SMD:R_0402_1005Metric,C844452,"Gain feedback. THIN FILM 0.1% 25ppm/C (Vishay TNPW040210K0BEED) - with R7/R9 these set G per bank, so a mismatch is a bank-to-bank gain error. Same reel as R1/R2"
"R7,R9",2k,Resistor_SMD:R_0402_1005Metric,C844262,"Gain set to GND. G = 1 + R6/R7 = 6. FIT ON TEST. THIN FILM 0.1% 25ppm/C (Vishay TNPW04022K00BEED), and ideally the same lot as R6/R8 so the two banks track"
"R11,R12",120R,Resistor_SMD:R_0603_1608Metric,C861094,"Bus termination. DNF except on the two end boards: make_fab.py leaves them out of the default assembly files and writes an end-board set. THIN FILM 0.1% 25ppm/C, 0.1 W (Yageo RT0603BRD07120RL); ~35 mW each at a 2 V differential"
R15,100k,Resistor_SMD:R_0402_1005Metric,C852472,"Rail monitor, top. THIN FILM 0.1% 25ppm/C (Yageo RT0402BRD07100KL)"
R16,47k,Resistor_SMD:R_0402_1005Metric,C728561,"Rail monitor, bottom. THIN FILM 0.1% 25ppm/C (Yageo RT0402BRD0747KL). (Was C25819, an 0603.)"
R17,1k,Resistor_SMD:R_0402_1005Metric,C852624,Status LED. THIN FILM 0.1% 25ppm/C (Yageo RT0402BRD071KL)
"R21,R22",51R,Resistor_SMD:R_0402_1005Metric,C852830,"Series into the RP2354A's ADC pin (GPIO27 / GPIO29), outside the feedback loop. With C31/C32 this is the charge reservoir the internal SAR's sample-and-hold needs; it sits at the MCU pin, so the long run from U7 is the amplifier's low-impedance output. THIN FILM 0.1% 25ppm/C (Yageo RT0402BRD0751RL). Never 5.1k: 5.1k x 1nF = 5.1 us, longer than a 2 us conversion"
R20,10k,Resistor_SMD:R_0402_1005Metric,C844452,RUN pull-up. The pin has a weak internal one; this makes it a net. THIN FILM 0.1% 25ppm/C (Vishay TNPW040210K0BEED)
"R23,R24",27R,Resistor_SMD:R_0402_1005Metric,C852682,"USB series termination, one per line, at the MCU end (the RP2350 design guide value). THIN FILM 0.1% 25ppm/C (Yageo RT0402BRD0727RL). LOW STOCK"
R25,1k,Resistor_SMD:R_0402_1005Metric,C852624,"BOOTSEL series. ~QSPI_SS is bonded to the stacked flash die, so the button is a stub on a live chip-select at up to 133 MHz; this keeps it behind a resistor. THIN FILM 0.1% 25ppm/C (Yageo RT0402BRD071KL)"
R26,10R,Resistor_SMD:R_0402_1005Metric,C705629,"ADC_AVDD filter, with C36. ADC_AVDD is the internal ADC's supply AND its reference, so in rev-4 it is the reference for the sensor reading: fed from +3.3V like ROW_VCC, so the code stays ratiometric. This keeps IOVDD switching noise off it. THIN FILM 0.1% 25ppm/C (Yageo RT0402BRD0710RL)"
C1-C7,100nF,Capacitor_SMD:C_0402_1005Metric,C85858,"Per-IC decoupling. Murata GCM155R71H104KE02D, X7R 50 V, AEC-Q200"
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
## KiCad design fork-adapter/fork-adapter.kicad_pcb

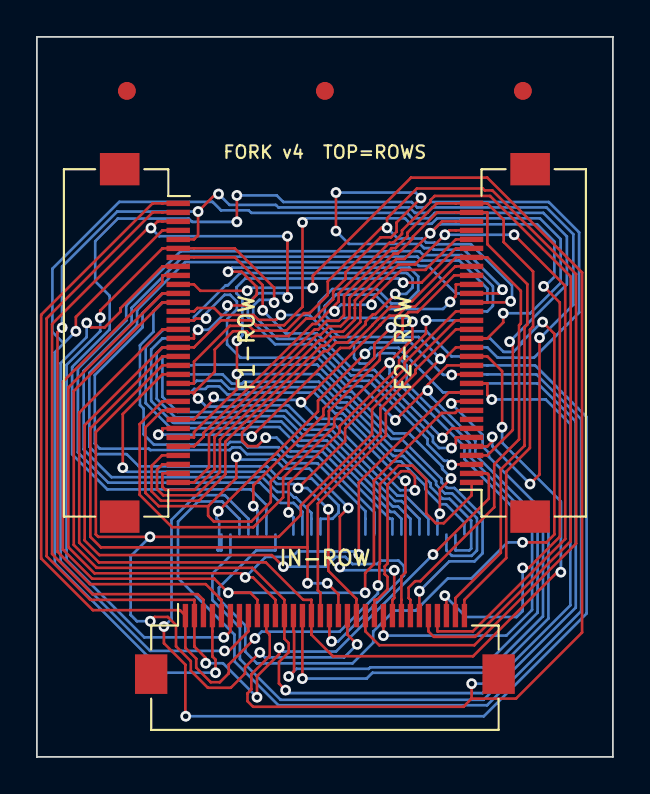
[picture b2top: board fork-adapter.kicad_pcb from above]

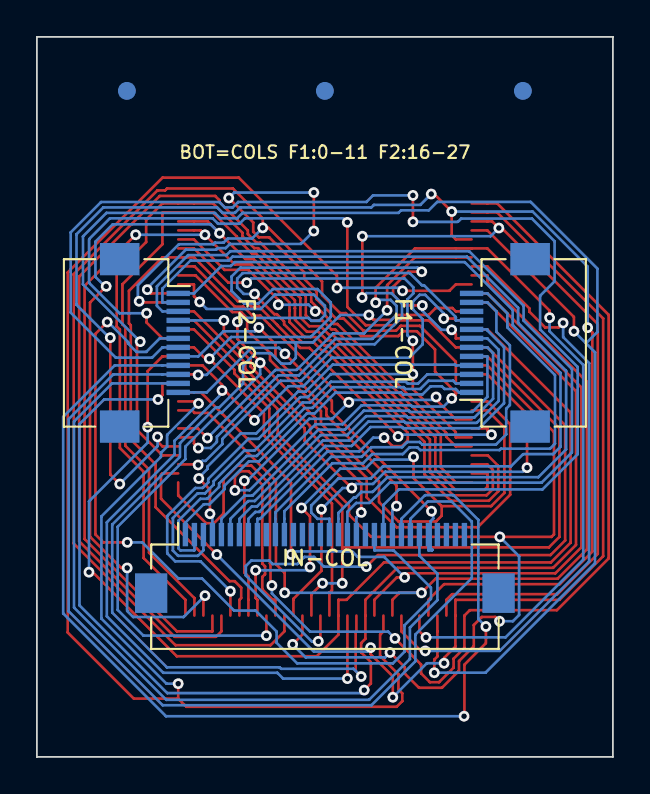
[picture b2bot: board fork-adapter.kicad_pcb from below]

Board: 2 copper layers, 32.0 x 40.0 mm, 12 parts (6 on the bottom side), 56 nets.

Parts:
FID1B, FID1T, FID2B, FID2T, FID3B, FID3T: Fiducial_1mm_Mask2mm
J1, J2, J3, J4: Hirose_FH12-32S-0.5SH_1x32-1MP_P0.50mm_Horizontal
J5, J6: Hirose_FH12-12S-0.5SH_1x12-1MP_P0.50mm_Horizontal

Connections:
COL_0: J2.1, J5.1
COL_1: J2.2, J5.2
COL_2: J2.3, J5.3
COL_3: J2.4, J5.4
COL_4: J2.5, J5.5
COL_5: J2.6, J5.6
COL_6: J2.7, J5.7
COL_7: J2.8, J5.8
COL_8: J2.9, J5.9
COL_9: J2.10, J5.10
COL_10: J2.11, J5.11
COL_11: J2.12, J5.12
COL_16: J2.17, J6.1
COL_17: J2.18, J6.2
COL_18: J2.19, J6.3
COL_19: J2.20, J6.4
COL_20: J2.21, J6.5
COL_21: J2.22, J6.6
COL_22: J2.23, J6.7
COL_23: J2.24, J6.8
COL_24: J2.25, J6.9
COL_25: J2.26, J6.10
COL_26: J2.27, J6.11
COL_27: J2.28, J6.12
ROW_0: J1.1, J3.1, J4.1
ROW_1: J1.2, J3.2, J4.2
ROW_2: J1.3, J3.3, J4.3
ROW_3: J1.4, J3.4, J4.4
ROW_4: J1.5, J3.5, J4.5
ROW_5: J1.6, J3.6, J4.6
ROW_6: J1.7, J3.7, J4.7
ROW_7: J1.8, J3.8, J4.8
ROW_8: J1.9, J3.9, J4.9
ROW_9: J1.10, J3.10, J4.10
ROW_10: J1.11, J3.11, J4.11
ROW_11: J1.12, J3.12, J4.12
ROW_12: J1.13, J3.13, J4.13
ROW_13: J1.14, J3.14, J4.14
ROW_14: J1.15, J3.15, J4.15
ROW_15: J1.16, J3.16, J4.16
ROW_16: J1.17, J3.17, J4.17
ROW_17: J1.18, J3.18, J4.18
ROW_18: J1.19, J3.19, J4.19
ROW_19: J1.20, J3.20, J4.20
ROW_20: J1.21, J3.21, J4.21
ROW_21: J1.22, J3.22, J4.22
ROW_22: J1.23, J3.23, J4.23
ROW_23: J1.24, J3.24, J4.24
ROW_24: J1.25, J3.25, J4.25
ROW_25: J1.26, J3.26, J4.26
ROW_26: J1.27, J3.27, J4.27
ROW_27: J1.28, J3.28, J4.28
ROW_28: J1.29, J3.29, J4.29
ROW_29: J1.30, J3.30, J4.30
ROW_30: J1.31, J3.31, J4.31
ROW_31: J1.32, J3.32, J4.32
